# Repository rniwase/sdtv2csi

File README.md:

# sdtv2csi - SDTV to MIPI CSI-2 Video Decoder
Board for converting SDTV analog video to MIPI CSI-2 using Analog Devices ADV7280A-M.

## Configuration example in Raspberry Pi 4
1. Get and run kernel patch installation scripts
```
wget https://github.com/rniwase/sdtv2csi/raw/master/rpi/install_patch.sh
sudo bash install_patch.sh
```

2. Set dtoverlay in config.txt
```
# for Raspberry Pi OS Bookworm:
sudo bash -c 'echo "dtoverlay=adv728x-m,adv7280m=1" >> /boot/firmware/config.txt'
# for Raspberry Pi OS Bullseye:
sudo bash -c 'echo "dtoverlay=adv728x-m,adv7280m=1" >> /boot/config.txt'
```

3. Reboot the system and check for devices.
```
sudo reboot
sudo v4l2-ctl --all -d /dev/video0
```

### Operation check by FFmpeg
1. Connect NTSC composite video signal to VIDEO_IN pin header AIN1-GND

2. Install FFmpeg
```
sudo apt update
sudo apt install ffmpeg
```

3. Video recording
```
# Record full video including blanking line
ffmpeg -an -video_size 720x507 -r 29.97 -i /dev/video0 -c:v rawvideo -vf realtime -t 5 out.asf
# Record video with blanking lines cropped
ffmpeg -an -video_size 720x507 -r 29.97 -i /dev/video0 -c:v rawvideo -vf realtime,crop=720:480:0:27 -t 5 out_crop.asf
```

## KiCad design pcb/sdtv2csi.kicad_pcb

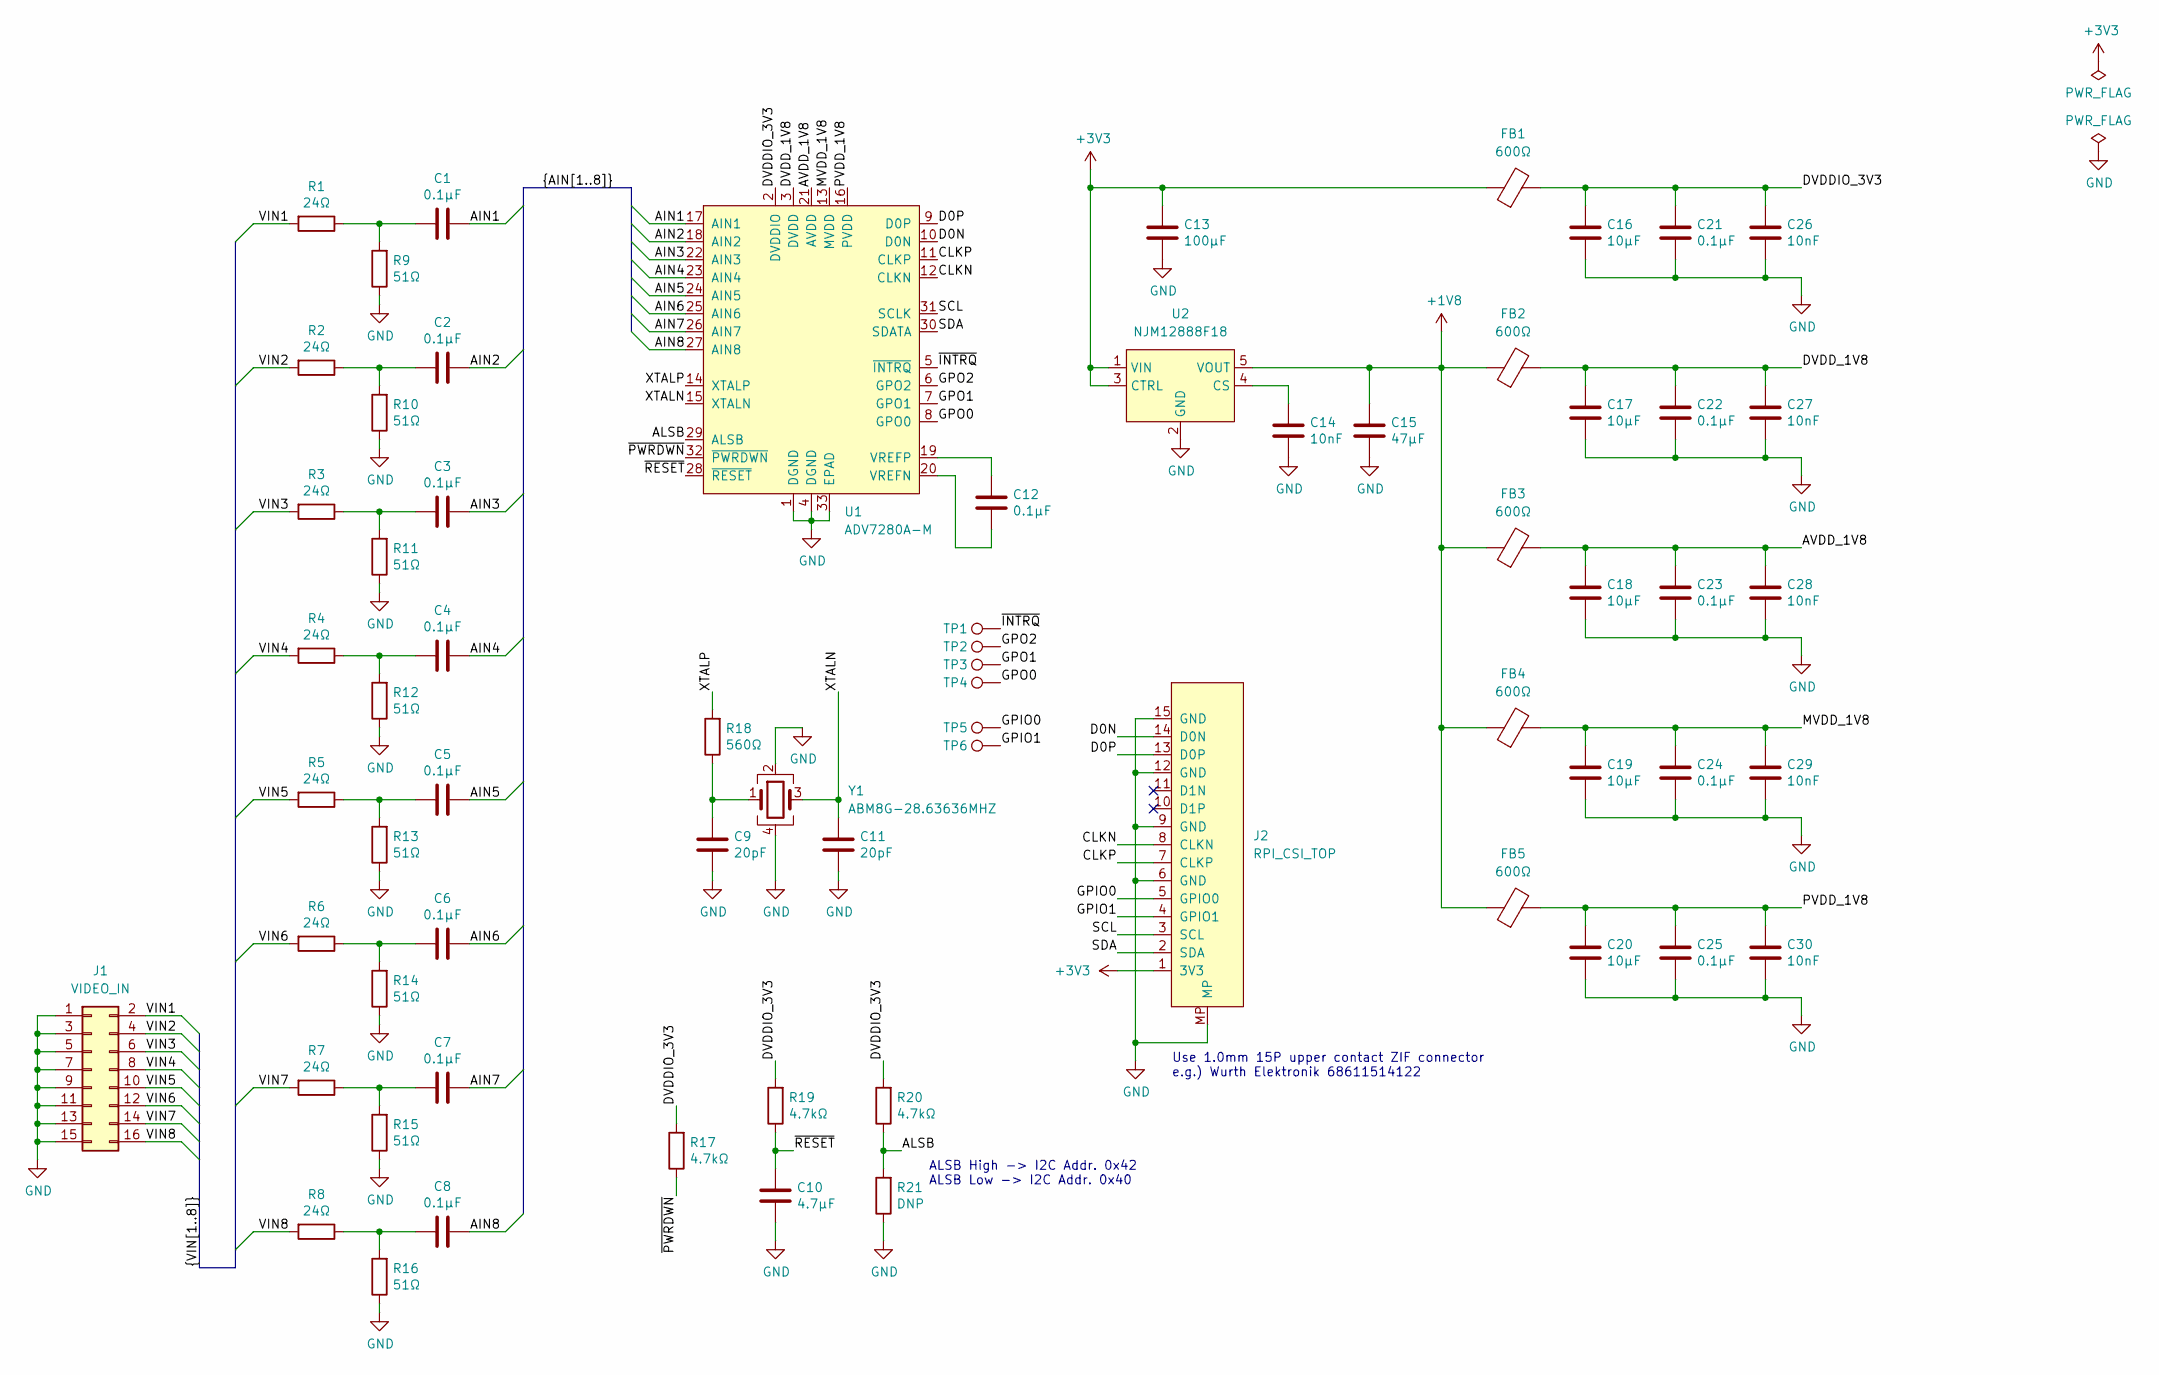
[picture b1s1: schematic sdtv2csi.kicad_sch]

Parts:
C1, C2, C3, C4, C5, C6, C7, C8, C12, C21, C22, C23, C24, C25: 0.1μF; C_0402_1005Metric
C9, C11: 20pF; C_0402_1005Metric
C10: 4.7μF; C_0402_1005Metric
C13: 100μF; C_1206_3216Metric
C14, C26, C27, C28, C29, C30: 10nF; C_0402_1005Metric
C15: 47μF; C_1206_3216Metric
C16, C17, C18, C19, C20: 10μF; C_0402_1005Metric
FB1, FB2, FB3, FB4, FB5: 600Ω; L_0603_1608Metric
J1: VIDEO_IN; PinHeader_2x08_P2.54mm_Vertical
J2: RPI_CSI_TOP; TE_1-84953-5_1x15-1MP_P1.0mm_Horizontal
R1, R2, R3, R4, R5, R6, R7, R8: 24Ω; R_0402_1005Metric
R9, R10, R11, R12, R13, R14, R15, R16: 51Ω; R_0402_1005Metric
R17, R19, R20: 4.7kΩ; R_0402_1005Metric
R18: 560Ω; R_0402_1005Metric
R21: DNP; R_0402_1005Metric
TP1, TP2, TP3, TP4, TP5, TP6: TestPoint; TestPoint_Pad_D1.0mm
U1: ADV7280A-M; LFCSP-32-1EP_5x5mm_P0.5mm_EP3.25x3.25mm
U2: NJM12888F18; SOT-23-5
Y1: ABM8G-28.63636MHZ; Crystal_SMD_3225-4Pin_3.2x2.5mm

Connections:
+1V8: C15.1, FB2.1, FB3.1, FB4.1, FB5.1, U2.5 (VOUT)
+3V3: C13.1, FB1.1, J2.1 (3V3), U2.1 (VIN), U2.3 (CTRL)
/AIN1: C1.1, U1.17 (AIN1)
/AIN2: C2.1, U1.18 (AIN2)
/AIN3: C3.1, U1.22 (AIN3)
/AIN4: C4.1, U1.23 (AIN4)
/AIN5: C5.1, U1.24 (AIN5)
/AIN6: C6.1, U1.25 (AIN6)
/AIN7: C7.1, U1.26 (AIN7)
/AIN8: C8.1, U1.27 (AIN8)
/ALSB: R20.1, R21.2, U1.29 (ALSB)
/AVDD_1V8: C18.1, C23.1, C28.1, FB3.2, U1.21 (AVDD)
/CLKN: J2.8 (CLKN), U1.12 (CLKN)
/CLKP: J2.7 (CLKP), U1.11 (CLKP)
/D0N: J2.14 (D0N), U1.10 (D0N)
/D0P: J2.13 (D0P), U1.9 (D0P)
/DVDDIO_3V3: C16.1, C21.1, C26.1, FB1.2, R17.2, R19.2, R20.2, U1.2 (DVDDIO)
/DVDD_1V8: C17.1, C22.1, C27.1, FB2.2, U1.3 (DVDD)
/GPIO0: J2.5 (GPIO0), TP5.1
/GPIO1: J2.4 (GPIO1), TP6.1
/GPO0: TP4.1, U1.8 (GPO0)
/GPO1: TP3.1, U1.7 (GPO1)
/GPO2: TP2.1, U1.6 (GPO2)
/MVDD_1V8: C19.1, C24.1, C29.1, FB4.2, U1.13 (MVDD)
/PVDD_1V8: C20.1, C25.1, C30.1, FB5.2, U1.16 (PVDD)
/SCL: J2.3 (SCL), U1.31 (SCLK)
/SDA: J2.2 (SDA), U1.30 (SDATA)
/VIN1: J1.2, R1.2
/VIN2: J1.4, R2.2
/VIN3: J1.6, R3.2
/VIN4: J1.8, R4.2
/VIN5: J1.10, R5.2
/VIN6: J1.12, R6.2
/VIN7: J1.14, R7.2
/VIN8: J1.16, R8.2
/XTALN: C11.1, U1.15 (XTALN), Y1.3
/XTALP: R18.2, U1.14 (XTALP)
/~INTRQ: TP1.1, U1.5 (~INTRQ)
/~PWRDWN: R17.1, U1.32 (~PWRDWN)
/~RESET: C10.1, R19.1, U1.28 (~RESET)
GND: C9.2, C10.2, C11.2, C13.2, C14.2, C15.2, C16.2, C17.2, C18.2, C19.2, C20.2, C21.2, C22.2, C23.2, C24.2, C25.2, C26.2, C27.2, C28.2, C29.2, C30.2, J1.1, J1.3, J1.5, J1.7, J1.9, J1.11, J1.13, J1.15, J2.6 (GND), J2.9 (GND), J2.12 (GND), J2.15 (GND), J2.MP, R9.1, R10.1, R11.1, R12.1, R13.1, R14.1, R15.1, R16.1, R21.1, U1.1 (DGND), U1.4 (DGND), U1.33 (EPAD), U2.2 (GND), Y1.2, Y1.4
unnamed: C1.2, R1.1, R9.2
unnamed: C2.2, R2.1, R10.2
unnamed: C3.2, R3.1, R11.2
unnamed: C4.2, R4.1, R12.2
unnamed: C5.2, R5.1, R13.2
unnamed: C6.2, R6.1, R14.2
unnamed: C7.2, R7.1, R15.2
unnamed: C8.2, R8.1, R16.2
unnamed: C9.1, R18.1, Y1.1
unnamed: C12.2, U1.20 (VREFN)
unnamed: C12.1, U1.19 (VREFP)
unnamed: C14.1, U2.4 (CS)

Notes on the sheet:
Use 1.0mm 15P upper contact ZIF connector e.g.) Wurth Elektronik 68611514122
ALSB High -> I2C Addr. 0x42 ALSB Low -> I2C Addr. 0x40

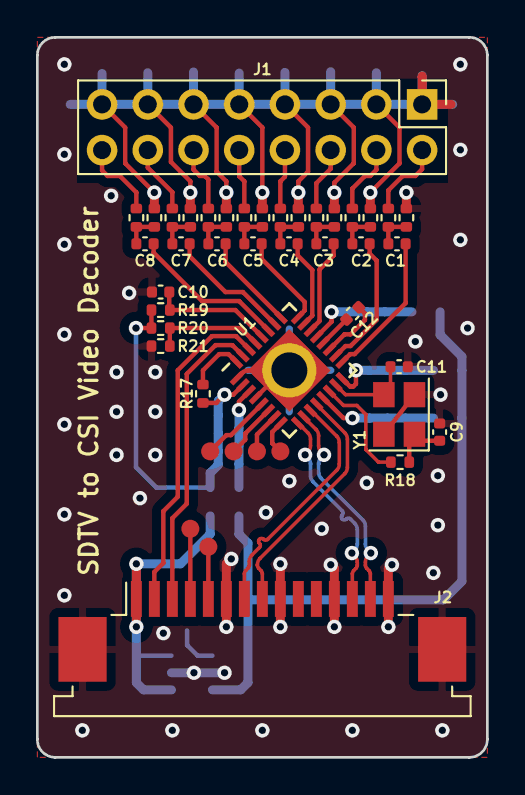
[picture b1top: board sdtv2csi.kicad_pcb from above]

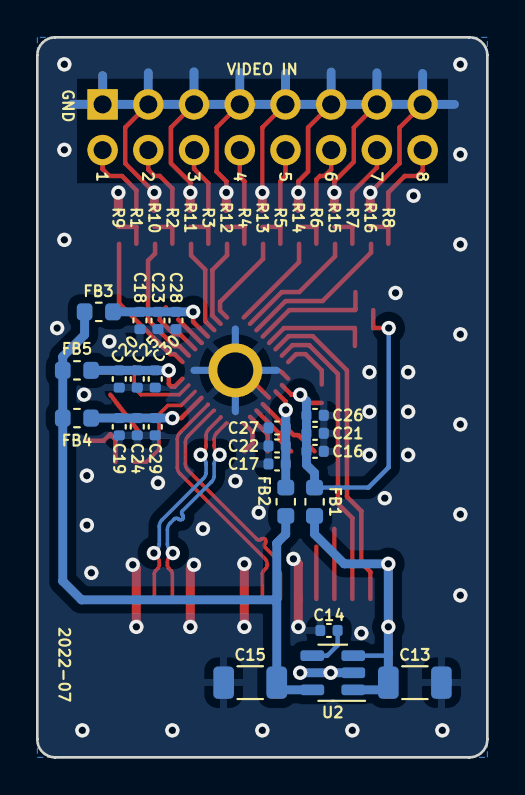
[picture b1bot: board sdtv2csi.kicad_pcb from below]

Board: 2 copper layers, 25.0 x 40.0 mm, 67 parts (24 on the bottom side), 53 nets.

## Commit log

2020-12-11 add .gitattributes
2022-07-05 migrate to KiCAD 6.0, update schematic wip
2022-07-07 update schematicand pcb, DRC passed
2022-07-07 place silkscreen
2022-07-09 update pcb
2022-07-09 clean up project, update pcb
2022-07-09 rename project
2022-10-12 add boardviews
2022-10-13 add example of operation
2024-08-02 add rpi/install_patch.sh
2024-08-02 update README.md for revised configuration procedures
2025-04-10 pcb: migrate KiCad to 9.0.1
